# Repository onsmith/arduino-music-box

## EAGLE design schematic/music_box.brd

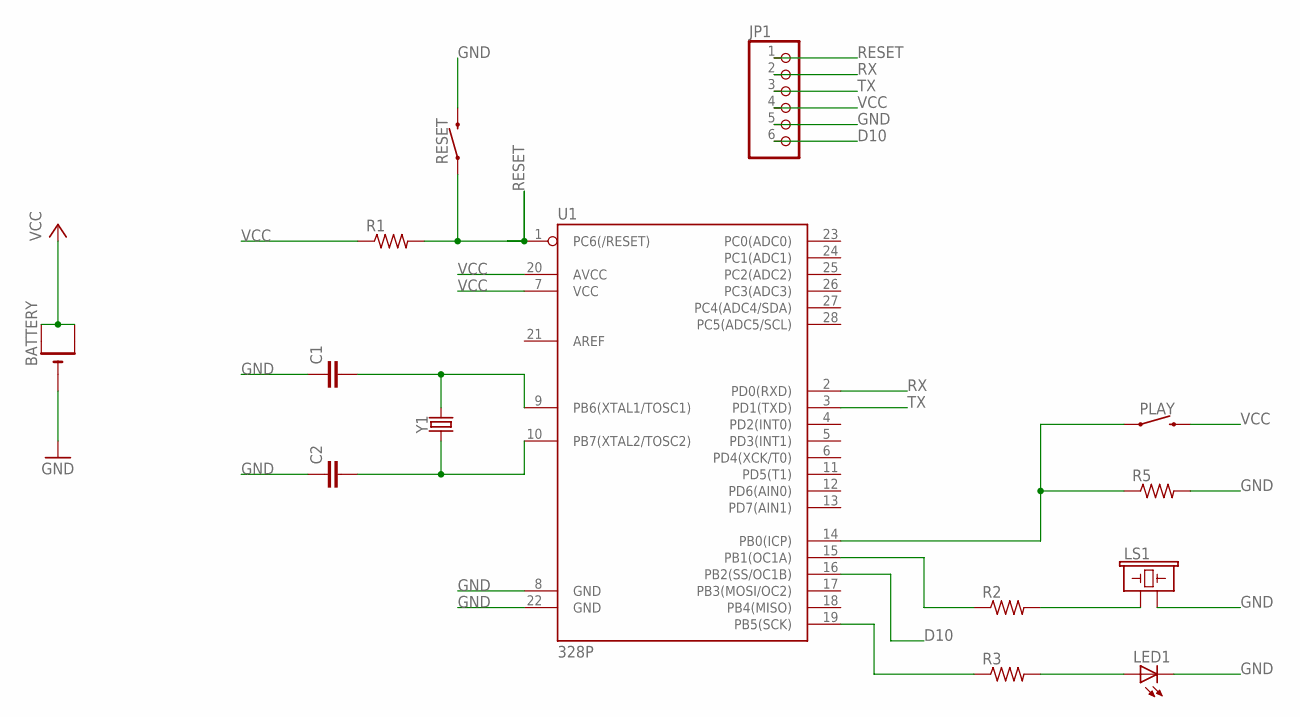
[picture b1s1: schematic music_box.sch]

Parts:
BATTERY: CR1220THM; CR1220-THM
C1, C2: 22PF-PTH-2.54MM-200V-5%; CAP-PTH-2.54
JP1: PINHD-1X6B; 1X06-BIG
LED1: LED5MM
LS1: BUZZER-PTH; BUZZER-12MM
PLAY: MOMENTARY-SWITCH-SPST-PTH-6.0MM; TACTILE_SWITCH_PTH_6.0MM
R1, R2, R3, R5: R-US_0207/7; 0207/7
RESET: MOMENTARY-SWITCH-SPST-PTH-6.0MM; TACTILE_SWITCH_PTH_6.0MM
U1: 328P; DIP28
Y1: CRYSTAL-16MHZPTH-HC49US; HC49US

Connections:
D10: JP1.6, U1.16 (PB2(SS/OC1B))
GND: BATTERY.-, C1.1, C2.1, JP1.5, LED1.K (C), LS1.- (2), R5.2, RESET.3 (2), U1.8 (GND), U1.22 (GND)
unnamed: R3.1, U1.19 (PB5(SCK))
unnamed: LS1.+ (1), R2.2
unnamed: LED1.A, R3.2
unnamed: R2.1, U1.15 (PB1(OC1A))
unnamed: PLAY.1, R5.1, U1.14 (PB0(ICP))
unnamed: C2.2, U1.10 (PB7(XTAL2/TOSC2)), Y1.1
unnamed: C1.2, U1.9 (PB6(XTAL1/TOSC1)), Y1.2
RESET: JP1.1, R1.2, RESET.1, U1.1 (PC6(/RESET))
RX: JP1.2, U1.2 (PD0(RXD))
TX: JP1.3, U1.3 (PD1(TXD))
VCC: BATTERY.+1 (+), BATTERY.+2 (+1), JP1.4, PLAY.3 (2), R1.1, U1.7 (VCC), U1.20 (AVCC)

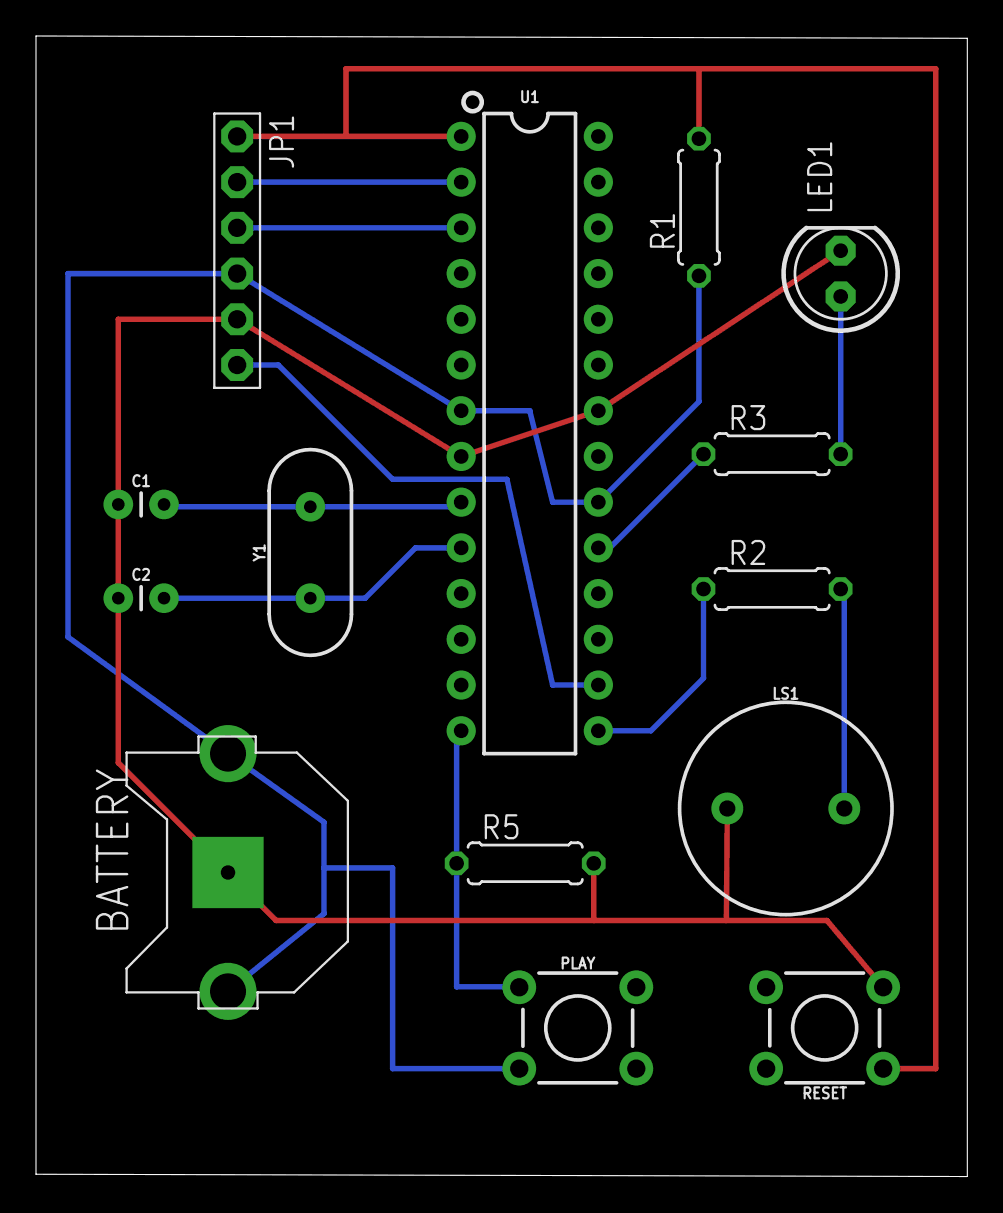
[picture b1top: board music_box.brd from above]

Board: 2 copper layers, 51.7 x 63.4 mm, 14 parts (0 on the bottom side), 13 nets.

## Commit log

2018-12-04 Final project

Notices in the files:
parts and their libraries:
SparkFun-Capacitors: Licensing: Creative Commons ShareAlike 4.0 International - https://creativecommons.org/licenses/by-sa/4.0
